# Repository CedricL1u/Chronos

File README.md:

# **Chronos \- A Mechanical Pomodoro Timer and Clock**

[Onshape CAD Link](https://cad.onshape.com/documents/4e46eab36ada7087591254e1/w/535417db20a99f0700b6b619/e/2bade0778d34ed4b7359ccd4?renderMode=0&uiState=6a28f4a51491e7cf1e2738ea)

# **Overview**

Chronos is a 7-Segment mechanical display that is supposed to function as a pomodoro timer,  clock, or as a regular timer. It’s equipped with speakers that play an alarm noise when time is up and also random sound effects throughout the timer. The speakers let the user know how many pomodoro cycles they have completed after each cycle. They also help Chronos function as an alarm clock when it is put into clock mode. On the top there are two buttons and a rotary encoder which serve as inputs to control it. Chronos is powered by a ESP32-C3 on a custom PCB that drives all the electronics. This device is named Chronos because in Greek it means the quantitative measurement of time that ticks away on a clock.

# **Why does this exist?**

Chronos was mainly built to function as a pomodoro timer, but since it has four numerical displays I decided to make it usable as a clock and regular timer as well. In case you don’t know what a Pomodoro timer is, it’s a simple timer that is used with the Pomodoro Technique. The Pomodoro Technique is a study strategy where you work in short focused intervals (usually 25 minutes) followed by brief breaks (about 5 minutes). You repeat this cycle four times and then you take a longer 15-30 minute break. It’s meant to help you stay focused, reduce procrastination, and make long tasks feel more manageable by splitting them into these repeating cycles. As a student myself who struggled with procrastination and locking in during study sessions I found the pomodoro technique to be extremely useful. I mainly used online timers I found but I found them to be kind of boring so I came up with this device. It’s extremely satisfying because it makes a click every time a digit changes and it’s also cool to see as I study. It’s kind of like an ASMR sound effect while I work or study.

# **Mechanics**

The clock works through four display modules each with seven segments. Each of these 7 segments are connected to a rack and pinion which drives each segment and controls when each segment is displayed and not displayed.  

Each of these racks are driven by a cam and follower mechanism that pushes each rack individually. There is a stack of 14 cams and each follower has 2 cams. One to retract it and one to extend it. Depending on the angle of the shaft different cams are extended and different cams are retracted which control the number displayed. Numbers are displayed at a 36 degree increment of the shaft. For example at 0 degrees the number 0 is displayed and at 72 degrees the number 2 is displayed.

The shaft is driven by a servo that is geared to it. 

# **Electronics**

This device is powered by a custom PCB I made in KiCAD that utilizes a Seed Studio XIAO ESP32-C3. On my board I have 4 servo pins which are driven by PWM signals from my microcontroller and the 5V power. There are also two MAX98357A Audio Drive ICs used to control the speakers on my device. I also have a 8-bit IO Expander IC because there weren’t enough GPIO pins on my microcontroller. The 8-Bit IO Expander communicates with my microcontroller through I2C and controls my rotary encoder switch and my two linear switches. The PCB is powered by a 8A 5V AC-DC unit that I plug into the wall and connect into my barrel jack connector. From there the power goes into a reverse polarity mosfet circuit that blocks current if the power supply is connected backwards. This P channel mosfet is then connected to my bulk 2200uF bulk capacitor that acts like a power reservoir to prevent brownouts in case the servos suddenly stall.  

# **Control**

There are 3 methods of input into the clock. A rotary encoder switch, and two cherry mx style linear mechanical keyboard switches. When you rotate the white knob in the middle you can change the duration of the timer when you are in the pomodoro or timer mode. When you click it you can pause or resume the clock. The right button lets you switch between clock mode, pomodoro mode, and timer mode. The left button lets you skip between pomodoro cycles.  

EC11EA5 Rotary Encoder Switch  

Cherry MX Style Linear Mechanical Keyboard Switch 

# **Bill of Materials**

[BOM File](https://github.com/CedricL1u/Chronos/blob/main/BOM.csv)

# **Assembly Instructions**

After you've printed all you're parts you want to first start by putting all of your fikkiwers into the front part of the casing. After you've done that you should align all of your cams on your shaft and place them all into their with your spacers. Once you've done that you need to put the cams into the followers. This can be a bit tricky, a tip I found useful was to wiggle the cams and move the followers when the cams get stuck. This can take a while but after you've done that you need to put the top plate on and screw it in, this will lock the shaft in place. After that mount the servo holder onto the back case plate and screw the servo onto the servo holder. Then screw in the servo gear and attach the back case plate into the rest of the case and align the followers such that they fit inside the hole. Repeat this 3 more times and you should have all 4 display modules. Once you have your display modules, you should first wire everything up. Wire all the jumper cables and servo wires from the pcb to their respective components. Then screw in the PCB and mount all 4 display modules, the 2 speakers, and then screw in the back plate for the case and you should be all good to go.

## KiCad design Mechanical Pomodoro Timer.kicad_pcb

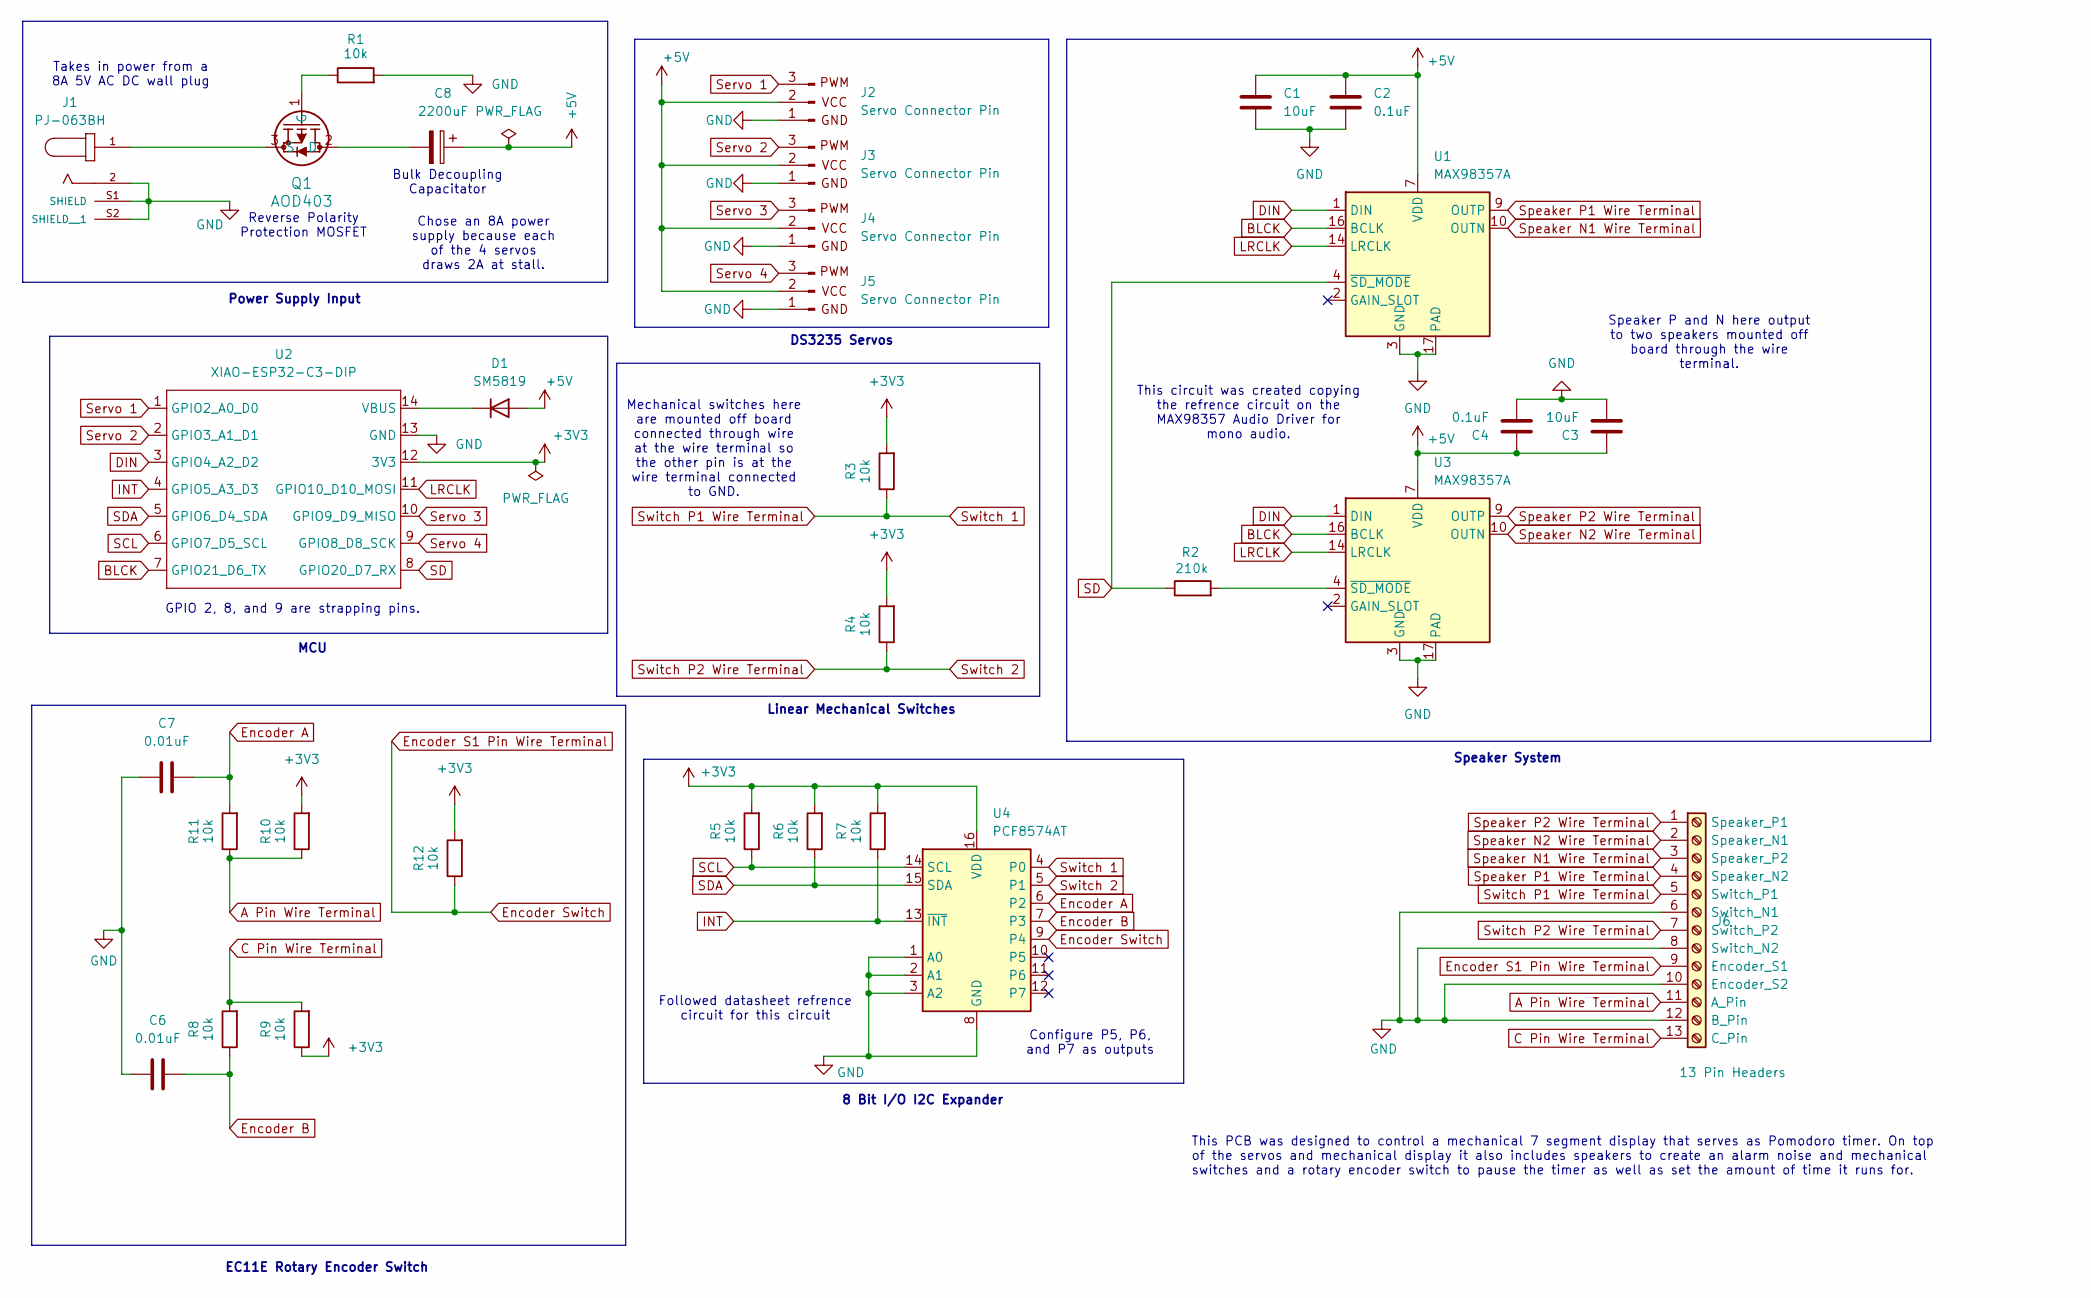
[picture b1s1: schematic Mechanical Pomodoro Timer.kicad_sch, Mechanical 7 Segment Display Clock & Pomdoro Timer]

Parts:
C1, C3: 10uF; C_0603_1608Metric_Pad1.08x0.95mm_HandSolder
C2, C4: 0.1uF; C_0603_1608Metric_Pad1.08x0.95mm_HandSolder
C6, C7: 0.01uF; C_0603_1608Metric_Pad1.08x0.95mm_HandSolder
C8: 2200uF; CAPPRD500W60D1250H2000
D1: SM5819; D_SOD-123F
J1: PJ-063BH; CUI_PJ-063BH; PARTREV 1.02
J2, J3, J4, J5: Servo Connector Pin; PinHeader_1x03_P2.54mm_Vertical
J6: 13 Pin Headers; PinHeader_1x13_P2.54mm_Vertical
Q1: AOD403; TO-252-3_TabPin2
R1, R3, R4, R5, R6, R7, R8, R9, R10, R11, R12: 10k; R_0603_1608Metric_Pad0.98x0.95mm_HandSolder
R2: 210k; R_0603_1608Metric_Pad0.98x0.95mm_HandSolder
U1, U3: MAX98357A; TQFN-16-1EP_3x3mm_P0.5mm_EP1.23x1.23mm
U2: XIAO-ESP32-C3-DIP; XIAO-ESP32-C3-SMD
U4: PCF8574AT; SOIC-16W_7.5x10.3mm_P1.27mm

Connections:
+3V3: R3.2, R4.2, R5.2, R6.2, R7.2, R9.1, R10.2, R12.2, U2.12 (3V3), U4.16 (VDD)
+5V: C1.1, C2.1, C3.1, C4.1, C8.P, D1.2 (A), J2.2, J3.2, J4.2, J5.2, U1.7 (VDD), U1.8 (VDD), U3.7 (VDD), U3.8 (VDD)
A Pin Wire Terminal: J6.11 (A_Pin), R10.1, R11.1
BLCK: U1.16 (BCLK), U2.7 (GPIO21_D6_TX), U3.16 (BCLK)
C Pin Wire Terminal: J6.13 (C_Pin), R8.2, R9.2
DIN: U1.1 (DIN), U2.3 (GPIO4_A2_D2), U3.1 (DIN)
Encoder A: C7.2, R11.2, U4.6 (P2)
Encoder B: C6.2, R8.1, U4.7 (P3)
Encoder S1 Pin Wire Terminal: J6.9 (Encoder_S1), R12.1, U4.9 (P4)
GND: C1.2, C2.2, C3.2, C4.2, C6.1, C7.1, J1.2, J1.S1 (SHIELD), J1.S2 (SHIELD__1), J2.1, J3.1, J4.1, J5.1, J6.6 (Switch_N1), J6.8 (Switch_N2), J6.10 (Encoder_S2), J6.12 (B_Pin), R1.2, U1.3 (GND), U1.11 (GND), U1.15 (GND), U1.17 (PAD), U2.13 (GND), U3.3 (GND), U3.11 (GND), U3.15 (GND), U3.17 (PAD), U4.1 (A0), U4.2 (A1), U4.3 (A2), U4.8 (GND)
INT: R7.1, U2.4 (GPIO5_A3_D3), U4.13 (~INT)
LRCLK: U1.14 (LRCLK), U2.11 (GPIO10_D10_MOSI), U3.14 (LRCLK)
unnamed: D1.1 (K), U2.14 (VBUS)
unnamed: C8.N, Q1.2 (D)
unnamed: Q1.1 (G), R1.1
unnamed: J1.1, Q1.3 (S)
unnamed: R2.2, U3.4 (~SD_MODE)
SCL: R5.1, U2.6 (GPIO7_D5_SCL), U4.14 (SCL)
SD: R2.1, U1.4 (~SD_MODE), U2.8 (GPIO20_D7_RX)
SDA: R6.1, U2.5 (GPIO6_D4_SDA), U4.15 (SDA)
Servo 1: J2.3, U2.1 (GPIO2_A0_D0)
Servo 2: J3.3, U2.2 (GPIO3_A1_D1)
Servo 3: J4.3, U2.10 (GPIO9_D9_MISO)
Servo 4: J5.3, U2.9 (GPIO8_D8_SCK)
Speaker N1 Wire Terminal: J6.3 (Speaker_P2), U1.10 (OUTN)
Speaker N2 Wire Terminal: J6.2 (Speaker_N1), U3.10 (OUTN)
Speaker P1 Wire Terminal: J6.4 (Speaker_N2), U1.9 (OUTP)
Speaker P2 Wire Terminal: J6.1 (Speaker_P1), U3.9 (OUTP)
Switch 1: J6.5 (Switch_P1), R3.1, U4.4 (P0)
Switch 2: J6.7 (Switch_P2), R4.1, U4.5 (P1)

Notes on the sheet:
This PCB was designed to control a mechanical 7 segment display that serves as Pomodoro timer. On top of the servos and mechanical display it also includes speakers to create an alarm noise and mechanical switches and a rotary encoder switch to pause the timer as well as set the amount of time it r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
This circuit was created copying the refrence circuit on the MAX98357 Audio Driver for mono audio.
DS3235 Servos
Linear Mechanical Switches
MCU
8 Bit I/O I2C Expander
Power Supply Input
Reverse Polarity Protection MOSFET
Speaker P and N here output to two speakers mounted off board through the wire terminal.
Takes in power from a 8A 5V AC DC wall plug
Bulk Decoupling Capacitator
Followed datasheet refrence circuit for this circuit
GPIO 2, 8, and 9 are strapping pins.
Chose an 8A power supply because each of the 4 servos draws 2A at stall.
EC11E Rotary Encoder Switch
Mechanical switches here are mounted off board connected through wire at the wire terminal so the other pin is at the wire terminal connected to GND.
Configure P5, P6, and P7 as outputs
Speaker System

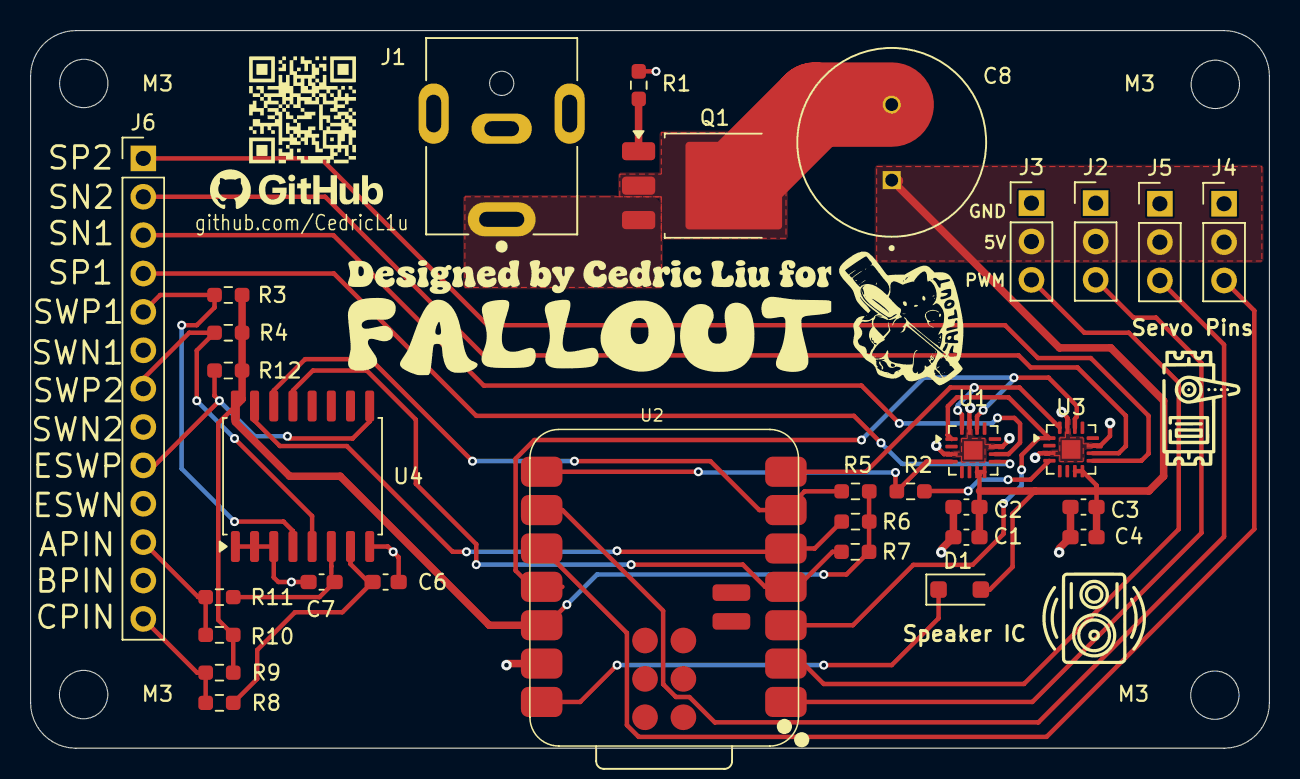
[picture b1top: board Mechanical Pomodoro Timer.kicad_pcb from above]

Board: 2 copper layers, 82.0 x 47.5 mm, 36 parts (0 on the bottom side), 30 nets.

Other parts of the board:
M3, M3#2, M3#3, M3#4: MountingHole_3.2mm_M3
Speakers: LOGO

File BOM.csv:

Product Name,Product Description,Product Link,Unit Price,Qty,Line Total,Running Total
PJ-063BH Power Barrel Jack (J1),Same Sky / PJ-063BH  |  2.5mm ID × 5.5mm OD  |  Right-angle THT,https://www.digikey.com/en/products/detail/same-sky-formerly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,$1.63000,1,$1.63,$1.63
"MAX98357AETE+T I2S Amplifier (U1, U3)",Analog Devices / MAX98357AETE+T  |  3.2W Class D Mono  |  TQFN-16,https://www.digikey.com/en/products/detail/analog-devices-in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,$3.73000,2,$7.46,$9.09
AS03104MR-F-WP-R Speaker (×2),PUI Audio / AS03104MR-F-WP-R  |  4Ω 3W Top-Port  |  94dB Waterproof,https://www.digikey.com/en/products/detail/pui-audio-inc/AS0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,$9.20000,2,$18.40,$27.49
SM5819PL-TP Schottky Diode (D1),MCC / SM5819PL-TP  |  40V 1A  |  SOD-123FL,https://www.digikey.com/en/products/detail/mcc-micro-commerc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,$0.21000,1,$0.21,$27.70
PCF8574ADWR I2C I/O Expander (U4),Texas Instruments / PCF8574ADWR  |  8-bit I2C 100kHz  |  SOIC-16,https://www.digikey.com/en/products/detail/texas-instruments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,$1.59000,1,$1.59,$29.29
"10µF 25V Ceramic Cap (C1, C3)",Murata / GRM188R61E106KA73D  |  0603 X5R  |  4 ordered,https://www.digikey.com/en/products/detail/murata-electronic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,$0.26000,4,$1.04,$30.33
"0.1µF 25V Ceramic Cap (C2, C4)",KEMET / C0603C104K3RACTU  |  0603 X7R  |  4 ordered,https://www.digikey.com/en/products/detail/kemet/C0603C104K3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,$0.10000,4,$0.40,$30.73
"10nF 50V Ceramic Cap (C6, C7)",KEMET / C0603C103K5RACTU  |  0603 X7R  |  4 ordered,https://www.digikey.com/en/products/detail/kemet/C0603C103K5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,$0.10000,4,$0.40,$31.13
2200µF 16V Electrolytic Cap (C8),Panasonic / EEU-FR1C222  |  Radial 20% 105°C  |  Qty 1,https://www.digikey.com/en/products/detail/panasonic-electro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,$1.67000,1,$1.67,$32.80
3-Pin Servo Header (J2–J5),Würth Elektronik / 61300311121  |  2.54mm vertical  |  4 ordered,https://www.digikey.com/en/products/detail/w%C3%BCrth-elektr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,$0.13000,4,$0.52,$33.32
13-Pin Header (J6),Würth Elektronik / 61301311121  |  2.54mm vertical  |  Qty 1,https://www.digikey.com/en/products/detail/w%C3%BCrth-elektr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,$0.75000,1,$0.75,$34.07
AOD403 P-Channel MOSFET (Q1),Alpha & Omega / AOD403  |  30V 15A/70A  |  TO-252  |  Qty 1,https://www.digikey.com/en/products/detail/alpha-omega-semic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,$2.05000,1,$2.05,$36.12
"10kΩ Resistor 0603 (R1, R3–R12)",YAGEO / RC0603FR-0710KL  |  10kΩ 1% 1/10W  |  15 ordered (11 needed per board),https://www.digikey.com/en/products/detail/yageo/RC0603FR-07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,$0.02500,15,$0.38,$36.50
210kΩ Resistor 0603 (R2),YAGEO / RC0603FR-07210KL  |  210kΩ 1% 1/10W  |  2 ordered (1 needed per board),https://www.digikey.com/en/products/detail/yageo/RC0603FR-07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,$0.10000,2,$0.20,$36.70
DigiKey — Shipping,,,$8.49,1,$8.49,$45.19
DigiKey — Tariff,,,$8.32,1,$8.32,$53.51
DigiKey — Sales Tax,,,$4.61,1,$4.61,$58.12
MG995 Metal Gear Servo — 4-Pack,"Deegoo-FPV  |  13KG metal gear, 180°, digital  |  Order 114-3366598-7401047",https://www.amazon.com/dp/B07NQJ1VZ2,$19.82000,1,$19.82,$77.94
ALITOVE 5V 8A 40W Power Supply,"ALITOVE  |  AC-DC 5V 8A, 5.5×2.5mm, 100–240V  |  Order 111-5079916-1830605",https://www.amazon.com/dp/B078RZBL8X,$20.39000,1,$20.39,$98.33
PCBS,Metromo Timer Gerbers_Y7  |  Order SO12606096033  |  5 boards,https://jlcpcb.com,$0.64000,5,$3.20,$101.53
Solder Paste Stencil,Metromo Timer Gerbers_Y7  |  Order SO12606096033  |  Qty 1,https://jlcpcb.com,$7.11000,1,$7.11,$108.64
JLCPCB — Shipping (net of discount),UPS Worldwide Express Saver (DDP)  |  $43.23 shipping − $15.00 discount,,$28.23,1,$28.23,$136.87
JLCPCB — Taxes,States Sales & Use Tax $0.10 + Import Taxes $0.74,,$0.84,1,$0.84,$137.71
XIAO ESP32-C3 DIP Module (U2),Seeed Studio XIAO ESP32-C3 DIP,https://www.seeedstudio.com/Seeed-XIAO-ESP32C3-p-5431.html,$10.69,1,$10.69,$148.40

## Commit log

2026-06-12 Add PlatformIO firmware project
2026-06-13 Fix image markdown syntax in README.md
2026-06-13 Add CAM-breakdown image to README
    Added CAM-breakdown image to README for clarity.
2026-06-14 hello
2026-06-14 Create LICENSE
